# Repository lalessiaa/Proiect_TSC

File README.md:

# Open book reader
Am proiectat un E-book reader, fiind construit in jurul microcontrolerului ESP32-C6, cu un incarcator USB-C si slot microSD.

Am urmat mai multi pasi in realizarea acestui poriect:
-	Crearea schematicului 
-	Am plasat componentele pe PCB
-	Am tras circuite si rutele
-	Incarcarea elementelor 3D pe PCB
-	Crearea bateriei si a display-ului
-	Inserarea bateriei, display-ului si a PCB-ului incarcasa 3D
  
# Functionalitati hardware
## ESP32-C6 
Este microcontroller-ul , el controleaza toate componentele si gestioneaza datele.
El foloseste mai multi pini printre care :
1)	Pentru comunicarea SPI cu viteza mare si numar redus de pini avem ( card SD ):   IO6 , IO7 (MOSI) , IO10 (CS) 
2)	Pentru a intra in mod de resetare rapida si mod de programare : IO0 - Buton BOOT , IO3 - Buton Reset
3)	External NOR Flash 64MB (SPI) pentru a extinde memoria: IO2 (MISO) , IO4 (CS) , IO6 (CLK/SCK) , IO7 (MOSI) 
4)	Battery Charge Level (GPIO) : IO12 

5)	Display Type Selector (GPIO): IO14

6)	Environmental Sensor BME688 (I2C) : IO8 (SCL), IO9 (SDA) 
7)	RTC Module DS3231SN (I2C) : IO8 (SCL) - linie de ceas I2C
IO9 (SDA) - linie de date I2C
8)	EPD Power (SPI) : IO6 (CLK/SCK), IO7 (MOSI), IO2 (MISO), IO5 (CS) 

1.	Senzorul de Mediu BME688
o	Interfață: I2C
o	Măsoară temperatura, umiditatea, presiunea, și compușii volatili organici pentru monitorizarea calității aerului.
2.	Memorie Externă NOR Flash 64MB
o	Interfață: SPI
o	Descriere: Folosită pentru stocarea datelor extinse și codului care nu se încadrează în memoria internă a ESP32.
o	Are consum redus în modul standby, crescând în timpul accesărilor de date.
3.	RTC (Real Time Clock) DS3231SN
o	Interfață: I2C
o	Menține timpul real chiar și în absența alimentării principale, utilizând o baterie de backup.
4.	Modulul de Încărcare a Bateriei
o	Interfață: GPIO (pentru monitorizarea stării)
o	Gestionează încărcarea bateriei Li-Po asigurând încărcare sigură și eficientă.
o	Are un consum mic, dependent de starea bateriei și de modul de încărcare.
5.	Regulator de Tensiune LDO
o	Regulează tensiunea de intrare pentru a asigura o alimentare stabilă de 3.3V pentru toate componentele.
Comunicații și Procesare
•	SPI: Utilizat pentru comunicații rapide cu memoria flash și display-ul E-Paper. Acest protocol este ideal pentru transferul de date la viteze înalte, esențial pentru performanța display-ului și accesul rapid la date.
•	I2C: Folosit pentru comunicația cu senzori de mediu și modulul RTC, care nu necesită viteze mari de transfer dar beneficiază de simplificarea conexiunilor.

# Bill of Materials
| Componenta    | Link | Datasheet
| -------- | ------- |--------|
|ESP32_WROVER_SPARKFUN-DISCRETESEMI_MOSFET_PCH-DMG2305UX-7|https://componentsearchengine.com/part-view/DMG2305UX-7/Diodes%20Incorporated|https://www.diodes.com//assets/Datasheets/DMG2305UX.pdf|
| QWIIC_CONNECTORJS-1MM | https://www.snapeda.com/parts/PRT-14417/SparkFun/view-part/     |https://www.snapeda.com/parts/PRT-14417/SparkFun%20Electronics/datasheet/
|CPH3225A|https://www.snapeda.com/parts/CPH3225A/Seiko+Instruments/view-part/?ref=eda|https://www.snapeda.com/parts/CPH3225A/Seiko%20Instruments/datasheet/|
|BUTTON_CUSYOMV1|https://industry.panasonic.com/global/en/downloads?tab=cad&small_g_cd=203&part_no=EVQPUJ02K&q=RVZRUFVKMDJLJTdDMTMlN0MyMDMlN0MzNDU5JTdDMSU3QyU3QyU3Q2ZhbHNl|https://industry.panasonic.com/global/en/downloads?tab=catalog&small_g_cd=203&part_no=EVQPUJ02K&q=RVZRUFVKMDJLJTdDMTMlN0MyMDMlN0MzNDU5JTdDMSU3QyU3QzIlN0NmYWxzZQ%3D%3D
|ESP32_WROVER_EAGLE-LTSPICE_CC0402|https://componentsearchengine.com/part-view/CC0402MRX5R5BB106/YAGEO|https://componentsearchengine.com/Datasheets/2/CC0402MRX5R5BB106.pdf
| ESP32_WROVER_EAGLE-LTSPICE_RR0402  | https://www.snapeda.com/parts/RC0402FR-07226RL/Yageo/view-part/    |https://www.snapeda.com/parts/RC0402FR-07226RL/Yageo/datasheet/
|BD5229G-TR|https://componentsearchengine.com/part-view/BD5229G-TR/ROHM%20Semiconductor|https://datasheet.datasheetarchive.com/originals/distributors/Datasheets_SAMA/f2b9741ef86007909f138d561a359946.pdf|
|DS3231SN|https://www.snapeda.com/parts/DS3231SN%23/Analog+Devices/view-part/?ref=eda|https://www.snapeda.com/parts/DS3231SN%23/Analog%20Devices/datasheet/|
|112A-TAAR-R03_ATTEND|https://store.comet.bg/en/Catalogue/Product/43497/|https://store.comet.bg/en/Catalogue/Product/43497/|
|744043680IND_4828-WE-TPC_WRE|https://www.digikey.sg/en/models/1638515|https://www.we-online.com/components/products/datasheet/744043680.pdf
|ESP32-C6-WROOM-1-N8|https://www.snapeda.com/parts/ESP32-C6-WROOM-1-N8/Espressif+Systems/view-part/?ref=eda|https://www.snapeda.com/parts/ESP32-C6-WROOM-1-N8/Espressif%20Systems/datasheet/
|ADAFRUIT_LEDCHIP-LED0603|https://www.snapeda.com/parts/KP-1608SURCK/Kingbright/view-part/?ref=search&t=LED%200603|https://www.snapeda.com/parts/KP-1608SURCK/Kingbright/datasheet/
|MCP73831|https://www.digikey.com/en/models/1874108|https://ww1.microchip.com/downloads/aemDocuments/documents/APID/ProductDocuments/DataSheets/MCP73831-Family-Data-Sheet-DS20001984H.pdf|
|XC6220A331MR-G|https://componentsearchengine.com/part-view/XC6220A331MR-G/Torex|https://product.torexsemi.com/system/files/series/xc6220.pdf|
|ESP32_WROVER_EAGLE-LTSPICE_CC0402|https://componentsearchengine.com/Datasheets/2/CC0402MRX5R5BB106.pdf|https://componentsearchengine.com/part-view/CC0402MRX5R5BB106/YAGEO|
|ESP32C6_VARISTORCN1812|https://www.mouser.co.uk/ProductDetail/EPCOS-TDK/B72520T0350K062?qs=dEfas%2FXlABIszF52uu7vrg%3D%3D|https://www.tdk-electronics.tdk.com/inf/75/db/CTVS_14/Surge_protection_series.pdf|
|MAX17048G+T10|https://www.snapeda.com/parts/MAX17048G+T10/Analog+Devices/view-part/?ref=eda|https://www.snapeda.com/parts/MAX17048G+T10/Analog%20Devices/datasheet/|
|PGB1010603MR|https://www.snapeda.com/parts/PGB1010603MR/Littelfuse/view-part/?ref=eda|https://www.snapeda.com/parts/PGB1010603MR/Littelfuse%20Inc./datasheet/|
|RCL_CPOL-EUCT3528|https://ro.mouser.com/ProductDetail/Vishay-Sprague/TR3B106K025C1300?qs=jCGqFXxTmLdffnuDkXzk1g%3D%3D|https://www.vishay.com/docs/40080/tr3.pdf|
|FH34SRJ-24S-0.5SH_99_|https://componentsearchengine.com/part-view/XC6220A331MR-G/Torex|https://product.torexsemi.com/system/files/series/xc6220.pdf|
|SAMACSYS_PARTS_USB4110-GF-A|https://componentsearchengine.com/part-view/USB4110-GF-A/GCT%20(GLOBAL%20CONNECTOR%20TECHNOLOGY)|https://gct.co/files/drawings/usb4110.pdf|
|SI1308EDL-T1-GE3|https://componentsearchengine.com/part-view/SI1308EDL-T1-GE3/Vishay|https://componentsearchengine.com/Datasheets/1/SI1308EDL-T1-GE3.pdf|
|MBR0530|https://ro.mouser.com/ProductDetail/KYOCERA-AVX/SD0805S020S1R0?qs=jCA%252BPfw4LHbpkAoSnwrdjw%3D%3D|https://ro.mouser.com/datasheet/2/40/schottky-3165252.pdf|
|SJ|https://grabcad.com/library/solder-jumpers-1||
|W25Q512JVEIQ|https://www.snapeda.com/parts/W25Q512JVEIQ/Winbond+Electronics/view-part/?ref=eda|https://www.snapeda.com/parts/W25Q512JVEIQ/Winbond%20Electronics/datasheet/|
|ESP32_WROVER_BME680_BME680|https://www.snapeda.com/parts/BME680/Bosch/view-part/?welcome=home|https://www.snapeda.com/parts/BME680/Bosch%20Sensortec/datasheet/|
|CPH3225A|https://www.snapeda.com/parts/CPH3225A/Seiko+Instruments/view-part/?ref=eda|https://www.snapeda.com/parts/CPH3225A/Seiko%20Instruments/datasheet/|
|USBLC6-2SC6Y|https://www.snapeda.com/parts/USBLC6-2SC6Y/STMicroelectronics/view-part/?ref=eda|https://www.snapeda.com/parts/USBLC6-2SC6Y/STMicroelectronics/datasheet/|

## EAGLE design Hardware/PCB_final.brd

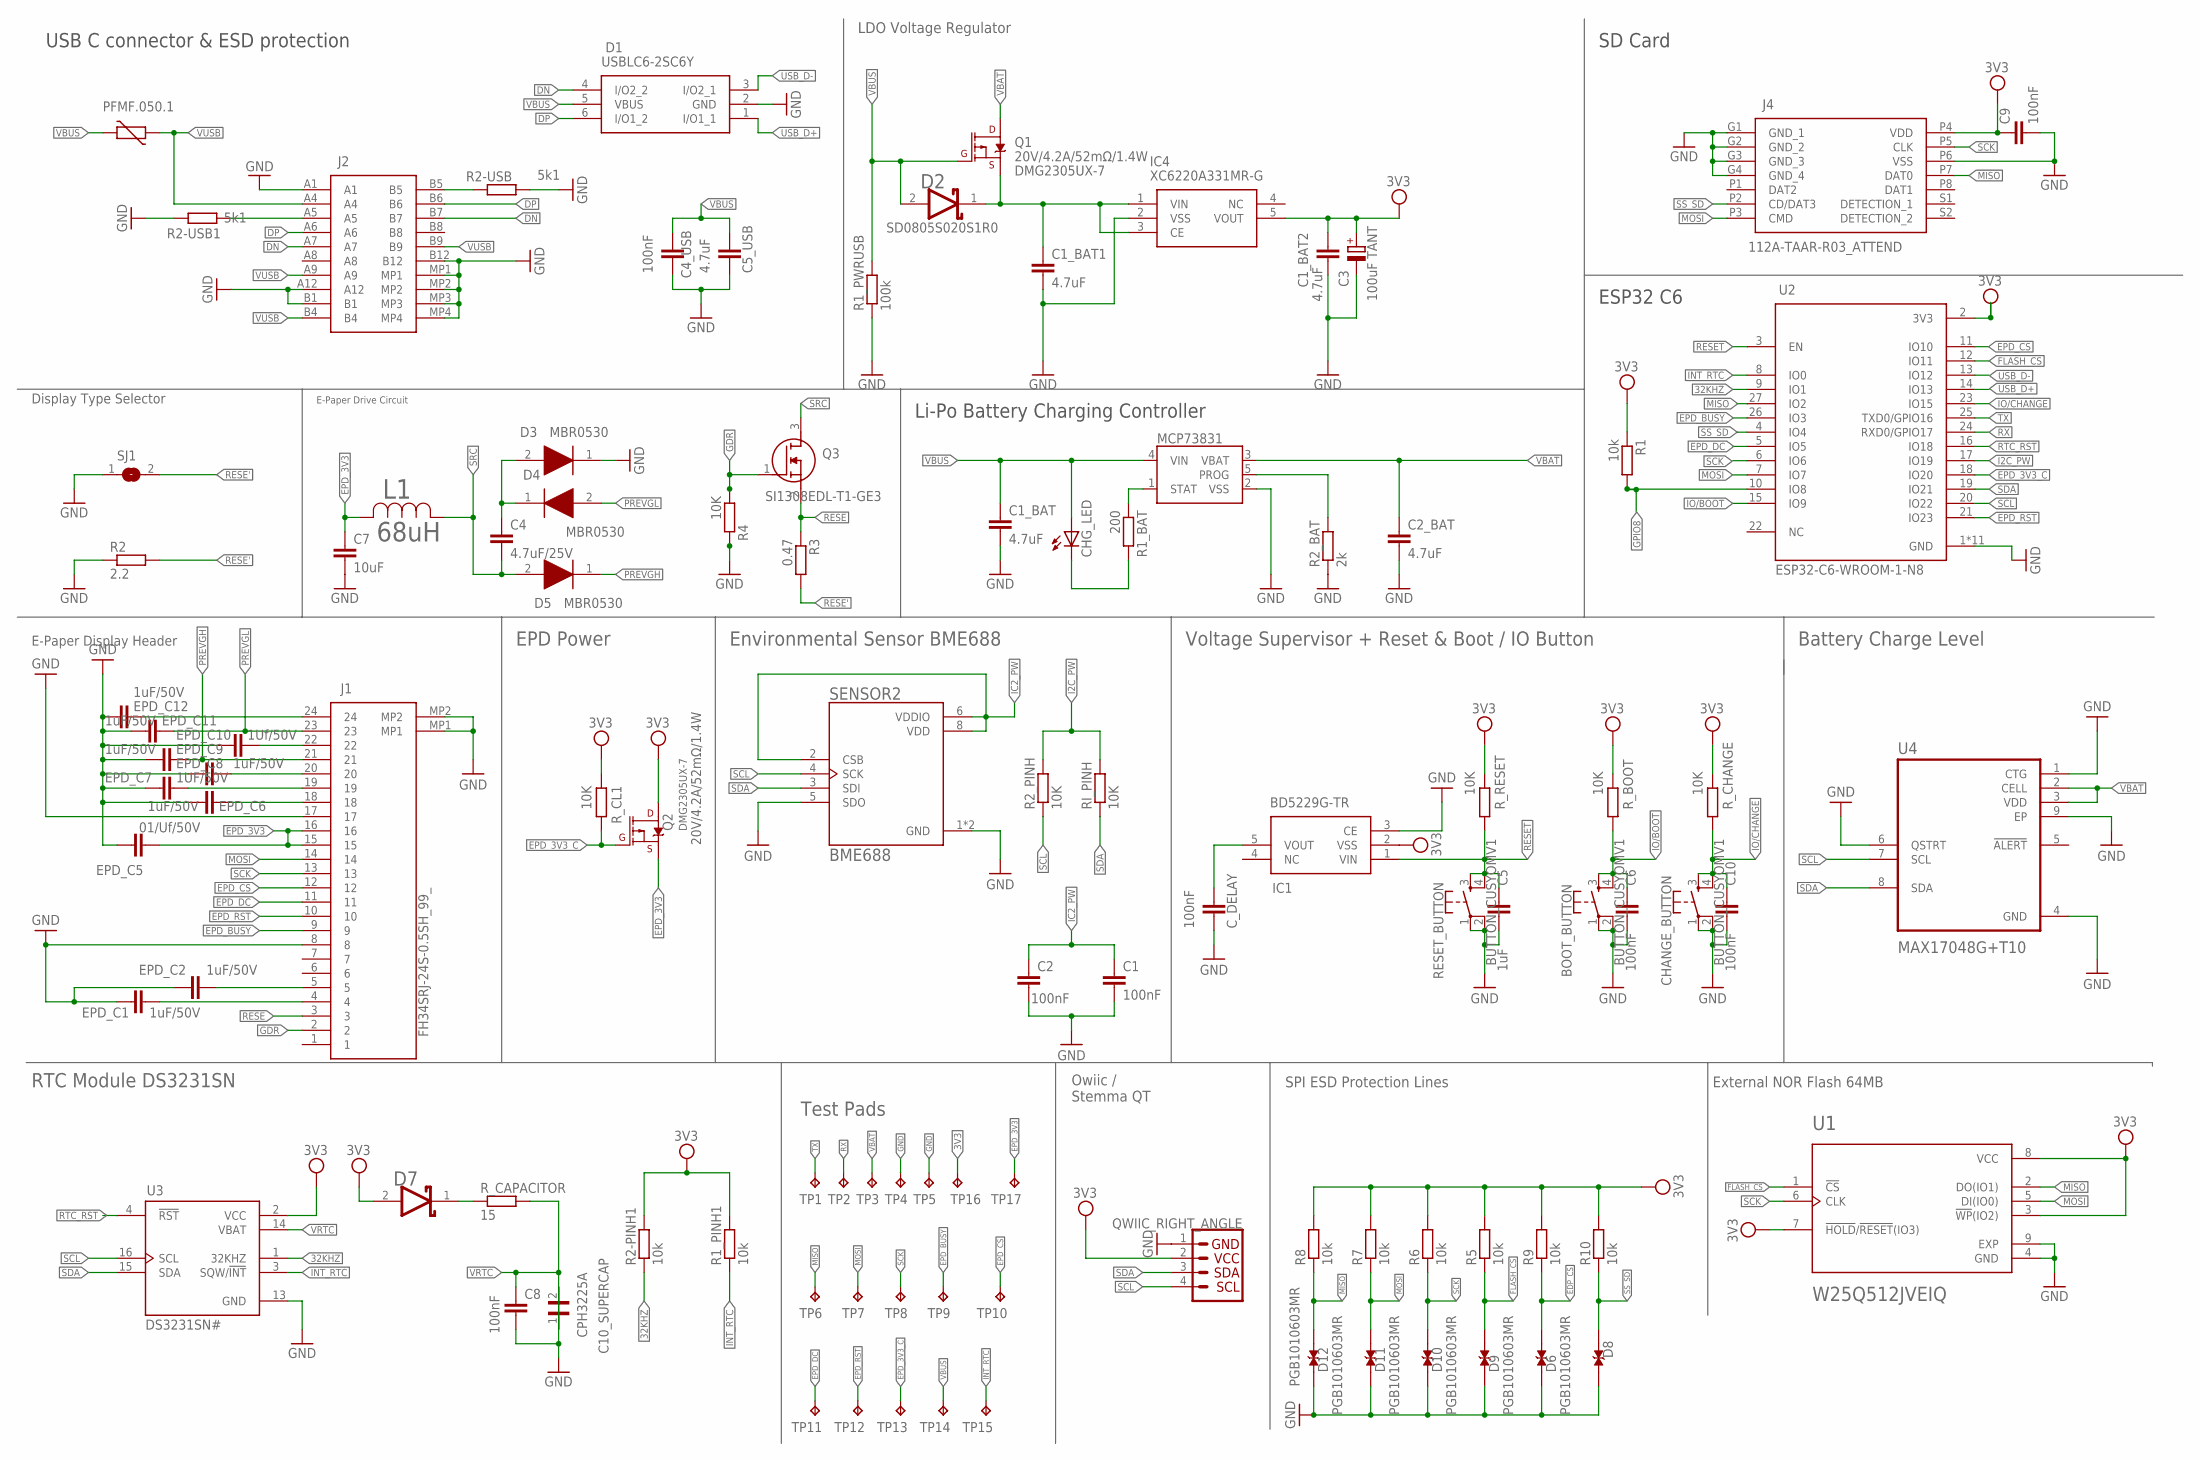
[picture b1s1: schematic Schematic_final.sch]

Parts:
BOOT_BUTTON: BUTTON_CUSYOMV1; MYBUTTON
C1, C2, C6, C8, C10: 100nF; ESP32_WROVER_EAGLE-LTSPICE_C0402
C1_BAT, C1_BAT2, C2_BAT: 4.7uF; ESP32_WROVER_EAGLE-LTSPICE_C0402
C1_BAT1, C5_USB: 4.7uF; EAGLE-LTSPICE_C0402
C3: 100uF TANT; RCL_CT3528
C4: 4.7uF/25V; ESP32_WROVER_EAGLE-LTSPICE_C0402
C4_USB, C9: 100nF; EAGLE-LTSPICE_C0402
C5: 1uF; ESP32_WROVER_EAGLE-LTSPICE_C0402
C7: 10uF; ESP32_WROVER_EAGLE-LTSPICE_C0402
C10_SUPERCAP: CPH3225A; CAPCP3225X100N
CHANGE_BUTTON: BUTTON_CUSYOMV1; MYBUTTON
CHG_LED: ADAFRUIT_LEDCHIP-LED0603; ADAFRUIT_CHIP-LED0603
C_DELAY: 100nF; ESP32_WROVER_EAGLE-LTSPICE_C0402
D1: USBLC6-2SC6Y; SOT95P280X145-6N
D2, D7: ESP32_WROVER_AVX---SD0805S020S1R0_AVX_SD0805S020S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; ESP32_WROVER_AVX---SD0805S020S1R0_AVX_SD0805S020S1R0_0
D3, D4, D5: MBR0530; SOD3716X135N
D6, D8, D9, D10, D11, D12: PGB1010603MR; DIOC1608X36N
EPD_C1, EPD_C2, EPD_C6, EPD_C8, EPD_C9, EPD_C11, EPD_C12: 1uF/50V; ESP32_WROVER_EAGLE-LTSPICE_C0402
EPD_C5: 01/Uf/50V; ESP32_WROVER_EAGLE-LTSPICE_C0402
EPD_C7: 1UF/50V; ESP32_WROVER_EAGLE-LTSPICE_C0402
EPD_C10: 1Uf/50V; ESP32_WROVER_EAGLE-LTSPICE_C0402
IC1: BD5229G-TR; SOT95P280X120-5N
IC4: XC6220A331MR-G; SOT95P280X120-5N
J1: FH34SRJ-24S-0.5SH_99_; FH34SRJ24S05SH99
J2: SAMACSYS_PARTS_USB4110-GF-A; SAMACSYS_PARTS_USB4110GFA
J3: QWIIC_RIGHT_ANGLE; JST04_1MM_RA
J4: 112A-TAAR-R03_ATTEND; 112ATAARR03ATTEND
L1: 68uH; IND_4828-WE-TPC_WRE
MCP73831: ESP32_WROVER_SPARKFUN-IC-POWER_MCP73831; ESP32_WROVER_SPARKFUN-IC-POWER_SOT23-5
PFMF.050.1: ESP32C6_VARISTORCN1812; ESP32C6_VARISTOR_CT/CN1812
Q1, Q2: 20V/4.2A/52mΩ/1.4W; ESP32_WROVER_SPARKFUN-DISCRETESEMI_SOT23-3
Q3: SI1308EDL-T1-GE3; SOT65P210X110-3N
R1, R1_PINH1, R2-PINH1, R5, R6, R7, R8, R9, R10: 10k; ESP32_WROVER_EAGLE-LTSPICE_R0402
R1_BAT: 200; ESP32_WROVER_EAGLE-LTSPICE_R0402
R1_PWRUSB: 100k; ESP32_WROVER_EAGLE-LTSPICE_R0402
R2: 2.2; ESP32_WROVER_EAGLE-LTSPICE_R0402
R2-USB, R2-USB1: 5k1; ESP32_WROVER_EAGLE-LTSPICE_R0402
R2_BAT: 2k; ESP32_WROVER_EAGLE-LTSPICE_R0402
R2_PINH, R4: 10K; ESP32_WROVER_EAGLE-LTSPICE_R0402
R3: 0.47; ESP32_WROVER_EAGLE-LTSPICE_R0402
RESET_BUTTON: BUTTON_CUSYOMV1; MYBUTTON
RI_PINH: 10K; ESP32_WROVER_EAGLE-LTSPICE_R0402
R_BOOT: 10K; ESP32_WROVER_EAGLE-LTSPICE_R0402
R_CAPACITOR: 15; ESP32_WROVER_EAGLE-LTSPICE_R0402
R_CHANGE: 10K; ESP32_WROVER_EAGLE-LTSPICE_R0402
R_CL1: 10K; ESP32_WROVER_EAGLE-LTSPICE_R0402
R_RESET: 10K; ESP32_WROVER_EAGLE-LTSPICE_R0402
SENSOR2: BME688; ESP32_WROVER_BME680_PSON80P300X300X100-8N
SJ1: SJ
TP1, TP2, TP3, TP4, TP5, TP6, TP7, TP8, TP9, TP10, TP11, TP12, TP13, TP14, TP15, TP16, TP17: TPTP20R; TP20R
U1: W25Q512JVEIQ; SON127P600X800X80-9N
U2: ESP32-C6-WROOM-1-N8; XCVR_ESP32-C6-WROOM-1-N8
U3: DS3231SN#; SOIC127P1032X265-16N
U4: MAX17048G+T10; SON50P200X200X80-9N

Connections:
3V3: C1_BAT2.1, C3.+, C9.1, D7.2 (ANODE), IC1.2 (VSS), IC4.5 (VOUT), J3.2, J4.P4 (VDD), Q2.3 (D), R1.1, R1_PINH1.2, R2-PINH1.2, R5.2, R6.2, R7.2, R8.2, R9.2, R10.2, R_BOOT.2, R_CHANGE.2, R_CL1.2, R_RESET.2, TP16.TP, U1.3 (!WP!(IO2)), U1.7 (!HOLD!/!RESET!(IO3)), U1.8 (VCC), U2.2 (3V3), U3.2 (VCC)
32KHZ: R2-PINH1.1, U2.9 (IO1), U3.1 (32KHZ)
DN: J2.A7
DP: J2.A6
EDP_CS: D9.2, R9.1
EPD_3V3: C7.1, EPD_C5.2, J1.15, J1.16, L1.2, Q2.2 (S), TP17.TP
EPD_3V3_C: Q2.1 (G), R_CL1.1, TP13.TP, U2.18 (IO20)
EPD_BUSY: J1.9, TP9.TP, U2.26 (IO3)
EPD_CS: J1.12, TP10.TP, U2.11 (IO10)
EPD_DC: J1.11, TP11.TP, U2.5 (IO5)
EPD_RST: J1.10, TP12.TP, U2.21 (IO23)
FLASH_CS: D10.2, R5.1, U1.1 (!CS), U2.12 (IO11)
GDR: J1.2, Q3.1 (G), R4.2
GND: BOOT_BUTTON.1, BOOT_BUTTON.2, C1.2, C1_BAT.2, C1_BAT1.2, C1_BAT2.2, C2.2, C2_BAT.2, C3.-, C4_USB.2, C5.2, C5_USB.2, C6.2, C7.2, C8.2, C9.2, C10.2, C10_SUPERCAP.2, CHANGE_BUTTON.1, CHANGE_BUTTON.2, C_DELAY.2, D1.2 (GND), D3.1 (K), D6.1, D8.1, D9.1, D10.1, D11.1, D12.1, EPD_C1.1, EPD_C2.1, EPD_C5.1, EPD_C6.2, EPD_C7.2, EPD_C8.2, EPD_C9.2, EPD_C10.2, EPD_C11.2, EPD_C12.2, IC1.3 (CE), IC4.2 (VSS), J1.8, J1.17, J1.MP1, J1.MP2, J2.A1, J2.A12, J2.B1, J2.B12, J2.MP1, J2.MP2, J2.MP3, J2.MP4, J3.1, J4.G1 (GND_1), J4.G2 (GND_2), J4.G3 (GND_3), J4.G4 (GND_4), J4.P6 (VSS), MCP73831.2 (VSS), R1_PWRUSB.1, R2.1, R2-USB.2, R2-USB1.1, R2_BAT.1, R4.1, RESET_BUTTON.1, RESET_BUTTON.2, SENSOR2.1 (GND), SENSOR2.5 (SDO), SENSOR2.7 (GND), SJ1.1, TP4.TP, TP5.TP, U1.4 (GND), U1.9 (EXP), U2.1 (GND), U2.28 (GND), U2.29_1 (GND), U2.29_2 (GND), U2.29_3 (GND), U2.29_4 (GND), U2.29_5 (GND), U2.29_6 (GND), U2.29_7 (GND), U2.29_8 (GND), U2.29_9 (GND), U3.13 (GND), U4.1 (CTG), U4.4 (GND), U4.6 (QSTRT), U4.9 (EP)
GPIO8: R1.2, U2.10 (IO8)
I2C_PW: R2_PINH.2, RI_PINH.2, U2.17 (IO19)
IC2_PW: C1.1, C2.1, SENSOR2.2 (CSB), SENSOR2.6 (VDDIO), SENSOR2.8 (VDD)
INT_RTC: R1_PINH1.1, TP15.TP, U2.8 (IO0), U3.3 (SQW/!INT)
IO/BOOT: BOOT_BUTTON.3, BOOT_BUTTON.4, C6.1, R_BOOT.1, U2.15 (IO9)
IO/CHANGE: C10.1, CHANGE_BUTTON.3, CHANGE_BUTTON.4, R_CHANGE.1, U2.23 (IO15)
MISO: D8.2, J4.P7 (DAT0), R8.1, TP6.TP, U1.2 (DO(IO1))
MOSI: D12.2, J1.14, J4.P3 (CMD), R7.1, TP7.TP, U1.5 (DI(IO0))
unnamed: J2.B5, R2-USB.1
unnamed: J2.A5, R2-USB1.2
unnamed: C_DELAY.1, IC1.5 (VOUT)
unnamed: EPD_C1.2, J1.4
unnamed: EPD_C2.2, J1.5
unnamed: EPD_C6.1, J1.18
unnamed: EPD_C7.1, J1.19
unnamed: EPD_C8.1, J1.20
unnamed: C4_USB.1, C5_USB.1
unnamed: EPD_C10.1, J1.22
unnamed: C1_BAT1.1, D2.1 (CATHODE), IC4.1 (VIN), IC4.3 (CE), Q1.2 (S)
unnamed: EPD_C12.1, J1.24
unnamed: D2.2 (ANODE), Q1.1 (G), R1_PWRUSB.2
unnamed: C4.2, D5.2 (A), L1.1
unnamed: C4.1, D3.2 (A), D4.1 (K)
unnamed: MCP73831.1 (STAT), R1_BAT.1
unnamed: CHG_LED.C, R1_BAT.2
unnamed: C1_BAT.1, CHG_LED.A, MCP73831.4 (VIN)
unnamed: MCP73831.5 (PROG), R2_BAT.2
unnamed: D7.1 (CATHODE), R_CAPACITOR.1
PREVGH: D5.1 (K), EPD_C9.1, J1.21
PREVGL: D4.2 (A), EPD_C11.1, J1.23
RESE: J1.3, Q3.2 (S), R3.1
RESE': SJ1.2
RESET: C5.1, IC1.1 (VIN), RESET_BUTTON.3, RESET_BUTTON.4, R_RESET.1, U2.3 (EN)
RTC_RST: U2.16 (IO18), U3.4 (!RST)
RX: TP2.TP, U2.24 (RXD0/GPIO17)
SCK: D11.2, J1.13, J4.P5 (CLK), R6.1, TP8.TP, U1.6 (CLK)
SCL: J3.4, R2_PINH.1, SENSOR2.4 (SCK), U2.20 (IO22), U3.16 (SCL), U4.7 (SCL)
SDA: J3.3, RI_PINH.1, SENSOR2.3 (SDI), U2.19 (IO21), U3.15 (SDA), U4.8 (SDA)
SRC: Q3.3 (D)
SS_SD: D6.2, J4.P2 (CD/DAT3), R10.1
TX: TP1.TP, U2.25 (TXD0/GPIO16)
USB_D+: D1.1 (I/O1_1), U2.14 (IO13)
USB_D-: D1.3 (I/O2_1), U2.13 (IO12)
VBAT: Q1.3 (D), TP3.TP, U4.2 (CELL), U4.3 (VDD)
VBBAT: C2_BAT.1, MCP73831.3 (VBAT)
VBUS: PFMF.050.1.2, TP14.TP
VRTC: C8.1, C10_SUPERCAP.1, R_CAPACITOR.2, U3.14 (VBAT)
VUSB: J2.A4, PFMF.050.1.1

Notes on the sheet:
DMG2305UX-7
USB C connector & ESD protection
SD Card
Li-Po Battery Charging Controller
ESP32 C6
Test Pads
EPD Power
Environmental Sensor BME688
Voltage Supervisor + Reset & Boot / IO Button
Battery Charge Level
SD0805S020S1R0
RTC Module DS3231SN
E-Paper Display Header
Display Type Selector
E-Paper Drive Circuit
SPI ESD Protection Lines
Owiic / Stemma QT
External NOR Flash 64MB
LDO Voltage Regulator

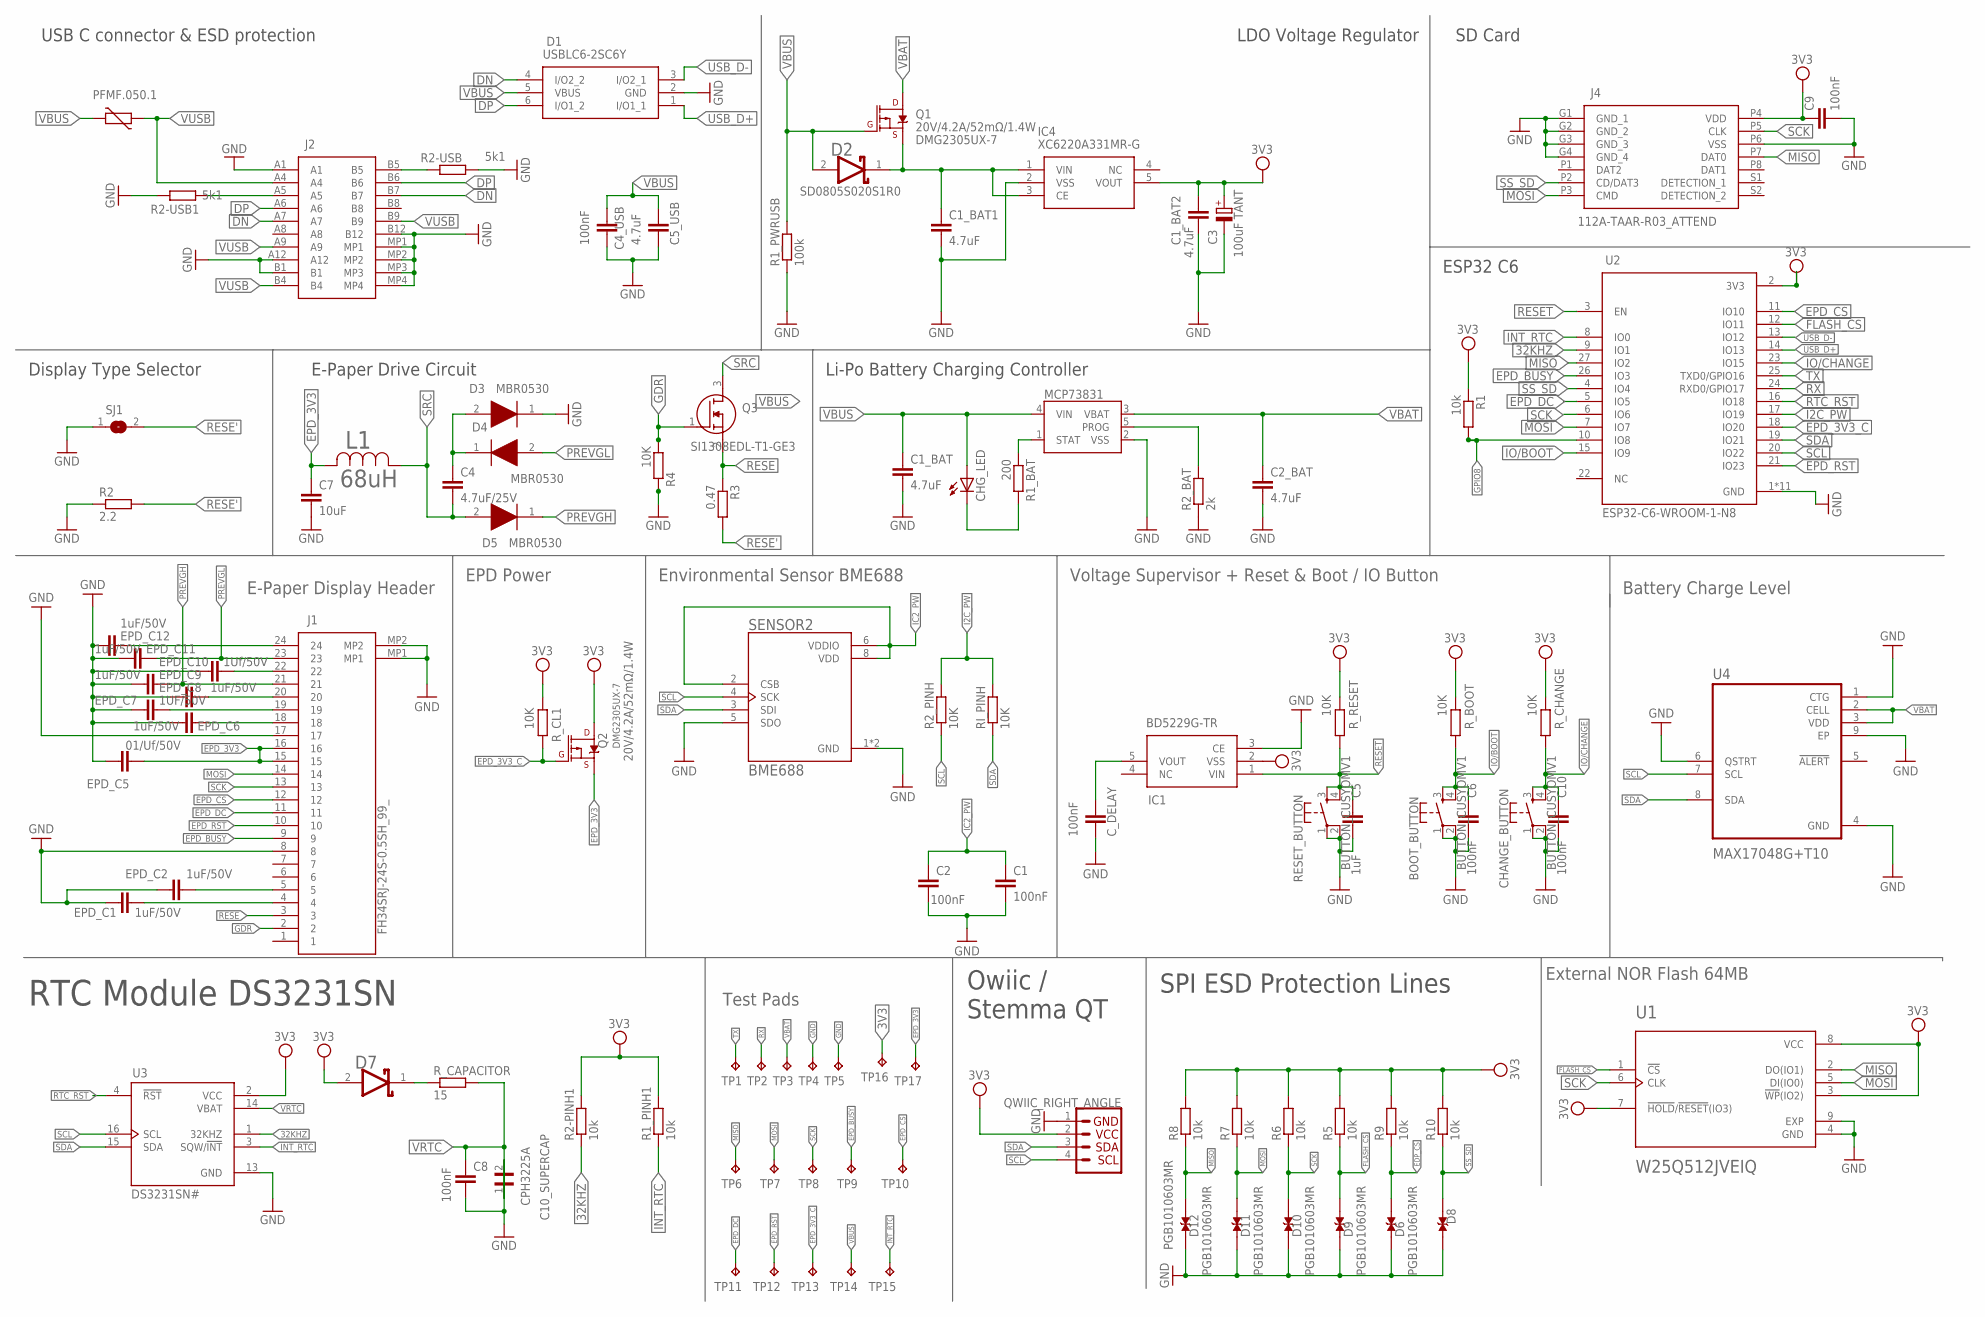
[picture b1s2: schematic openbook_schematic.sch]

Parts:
BOOT_BUTTON: BUTTON_CUSYOMV1; MYBUTTON
C1, C2, C6, C8, C10: 100nF; ESP32_WROVER_EAGLE-LTSPICE_C0402
C1_BAT, C1_BAT2, C2_BAT: 4.7uF; ESP32_WROVER_EAGLE-LTSPICE_C0402
C1_BAT1, C5_USB: 4.7uF; EAGLE-LTSPICE_C0402
C3: 100uF TANT; RCL_CT3528
C4: 4.7uF/25V; ESP32_WROVER_EAGLE-LTSPICE_C0402
C4_USB, C9: 100nF; EAGLE-LTSPICE_C0402
C5: 1uF; ESP32_WROVER_EAGLE-LTSPICE_C0402
C7: 10uF; ESP32_WROVER_EAGLE-LTSPICE_C0402
C10_SUPERCAP: CPH3225A; CAPCP3225X100N
CHANGE_BUTTON: BUTTON_CUSYOMV1; MYBUTTON
CHG_LED: ADAFRUIT_LEDCHIP-LED0603; ADAFRUIT_CHIP-LED0603
C_DELAY: 100nF; ESP32_WROVER_EAGLE-LTSPICE_C0402
D1: USBLC6-2SC6Y; SOT95P280X145-6N
D2, D7: ESP32_WROVER_AVX---SD0805S020S1R0_AVX_SD0805S020S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; ESP32_WROVER_AVX---SD0805S020S1R0_AVX_SD0805S020S1R0_0
D3, D4, D5: MBR0530; SOD3716X135N
D6, D8, D9, D10, D11, D12: PGB1010603MR; DIOC1608X36N
EPD_C1, EPD_C2, EPD_C6, EPD_C8, EPD_C9, EPD_C11, EPD_C12: 1uF/50V; ESP32_WROVER_EAGLE-LTSPICE_C0402
EPD_C5: 01/Uf/50V; ESP32_WROVER_EAGLE-LTSPICE_C0402
EPD_C7: 1UF/50V; ESP32_WROVER_EAGLE-LTSPICE_C0402
EPD_C10: 1Uf/50V; ESP32_WROVER_EAGLE-LTSPICE_C0402
IC1: BD5229G-TR; SOT95P280X120-5N
IC4: XC6220A331MR-G; SOT95P280X120-5N
J1: FH34SRJ-24S-0.5SH_99_; FH34SRJ24S05SH99
J2: SAMACSYS_PARTS_USB4110-GF-A; SAMACSYS_PARTS_USB4110GFA
J3: QWIIC_RIGHT_ANGLE; JST04_1MM_RA
J4: 112A-TAAR-R03_ATTEND; 112ATAARR03ATTEND
L1: 68uH; IND_4828-WE-TPC_WRE
MCP73831: ESP32_WROVER_SPARKFUN-IC-POWER_MCP73831; ESP32_WROVER_SPARKFUN-IC-POWER_SOT23-5
PFMF.050.1: ESP32C6_VARISTORCN1812; ESP32C6_VARISTOR_CT/CN1812
Q1, Q2: 20V/4.2A/52mΩ/1.4W; ESP32_WROVER_SPARKFUN-DISCRETESEMI_SOT23-3
Q3: SI1308EDL-T1-GE3; SOT65P210X110-3N
R1, R1_PINH1, R2-PINH1, R5, R6, R7, R8, R9, R10: 10k; ESP32_WROVER_EAGLE-LTSPICE_R0402
R1_BAT: 200; ESP32_WROVER_EAGLE-LTSPICE_R0402
R1_PWRUSB: 100k; ESP32_WROVER_EAGLE-LTSPICE_R0402
R2: 2.2; ESP32_WROVER_EAGLE-LTSPICE_R0402
R2-USB, R2-USB1: 5k1; ESP32_WROVER_EAGLE-LTSPICE_R0402
R2_BAT: 2k; ESP32_WROVER_EAGLE-LTSPICE_R0402
R2_PINH, R4: 10K; ESP32_WROVER_EAGLE-LTSPICE_R0402
R3: 0.47; ESP32_WROVER_EAGLE-LTSPICE_R0402
RESET_BUTTON: BUTTON_CUSYOMV1; MYBUTTON
RI_PINH: 10K; ESP32_WROVER_EAGLE-LTSPICE_R0402
R_BOOT: 10K; ESP32_WROVER_EAGLE-LTSPICE_R0402
R_CAPACITOR: 15; ESP32_WROVER_EAGLE-LTSPICE_R0402
R_CHANGE: 10K; ESP32_WROVER_EAGLE-LTSPICE_R0402
R_CL1: 10K; ESP32_WROVER_EAGLE-LTSPICE_R0402
R_RESET: 10K; ESP32_WROVER_EAGLE-LTSPICE_R0402
SENSOR2: BME688; ESP32_WROVER_BME680_PSON80P300X300X100-8N
SJ1: SJ
TP1, TP2, TP3, TP4, TP5, TP6, TP7, TP8, TP9, TP10, TP11, TP12, TP13, TP14, TP15, TP16, TP17: TPTP20R; TP20R
U1: W25Q512JVEIQ; SON127P600X800X80-9N
U2: ESP32-C6-WROOM-1-N8; XCVR_ESP32-C6-WROOM-1-N8
U3: DS3231SN#; SOIC127P1032X265-16N
U4: MAX17048G+T10; SON50P200X200X80-9N

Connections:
3V3: C1_BAT2.1, C3.+, C9.1, D7.2 (ANODE), IC1.2 (VSS), IC4.5 (VOUT), J3.2, J4.P4 (VDD), Q2.3 (D), R1.1, R1_PINH1.2, R2-PINH1.2, R5.2, R6.2, R7.2, R8.2, R9.2, R10.2, R_BOOT.2, R_CHANGE.2, R_CL1.2, R_RESET.2, TP16.TP, U1.3 (!WP!(IO2)), U1.7 (!HOLD!/!RESET!(IO3)), U1.8 (VCC), U2.2 (3V3), U3.2 (VCC)
32KHZ: R2-PINH1.1, U2.9 (IO1), U3.1 (32KHZ)
DN: J2.A7
DP: J2.A6
EDP_CS: D9.2, R9.1
EPD_3V3: C7.1, EPD_C5.2, J1.15, J1.16, L1.2, Q2.2 (S), TP17.TP
EPD_3V3_C: Q2.1 (G), R_CL1.1, TP13.TP, U2.18 (IO20)
EPD_BUSY: J1.9, TP9.TP, U2.26 (IO3)
EPD_CS: J1.12, TP10.TP, U2.11 (IO10)
EPD_DC: J1.11, TP11.TP, U2.5 (IO5)
EPD_RST: J1.10, TP12.TP, U2.21 (IO23)
FLASH_CS: D10.2, R5.1, U1.1 (!CS), U2.12 (IO11)
GDR: J1.2, Q3.1 (G), R4.2
GND: BOOT_BUTTON.1, BOOT_BUTTON.2, C1.2, C1_BAT.2, C1_BAT1.2, C1_BAT2.2, C2.2, C2_BAT.2, C3.-, C4_USB.2, C5.2, C5_USB.2, C6.2, C7.2, C8.2, C9.2, C10.2, C10_SUPERCAP.2, CHANGE_BUTTON.1, CHANGE_BUTTON.2, C_DELAY.2, D1.2 (GND), D3.1 (K), D6.1, D8.1, D9.1, D10.1, D11.1, D12.1, EPD_C1.1, EPD_C2.1, EPD_C5.1, EPD_C6.2, EPD_C7.2, EPD_C8.2, EPD_C9.2, EPD_C10.2, EPD_C11.2, EPD_C12.2, IC1.3 (CE), IC4.2 (VSS), J1.8, J1.17, J1.MP1, J1.MP2, J2.A1, J2.A12, J2.B1, J2.B12, J2.MP1, J2.MP2, J2.MP3, J2.MP4, J3.1, J4.G1 (GND_1), J4.G2 (GND_2), J4.G3 (GND_3), J4.G4 (GND_4), J4.P6 (VSS), MCP73831.2 (VSS), R1_PWRUSB.1, R2.1, R2-USB.2, R2-USB1.1, R2_BAT.1, R4.1, RESET_BUTTON.1, RESET_BUTTON.2, SENSOR2.1 (GND), SENSOR2.5 (SDO), SENSOR2.7 (GND), SJ1.1, TP4.TP, TP5.TP, U1.4 (GND), U1.9 (EXP), U2.1 (GND), U2.28 (GND), U2.29_1 (GND), U2.29_2 (GND), U2.29_3 (GND), U2.29_4 (GND), U2.29_5 (GND), U2.29_6 (GND), U2.29_7 (GND), U2.29_8 (GND), U2.29_9 (GND), U3.13 (GND), U4.1 (CTG), U4.4 (GND), U4.6 (QSTRT), U4.9 (EP)
GPIO8: R1.2, U2.10 (IO8)
I2C_PW: R2_PINH.2, RI_PINH.2, U2.17 (IO19)
IC2_PW: C1.1, C2.1, SENSOR2.2 (CSB), SENSOR2.6 (VDDIO), SENSOR2.8 (VDD)
INT_RTC: R1_PINH1.1, TP15.TP, U2.8 (IO0), U3.3 (SQW/!INT)
IO/BOOT: BOOT_BUTTON.3, BOOT_BUTTON.4, C6.1, R_BOOT.1, U2.15 (IO9)
IO/CHANGE: C10.1, CHANGE_BUTTON.3, CHANGE_BUTTON.4, R_CHANGE.1, U2.23 (IO15)
MISO: D8.2, J4.P7 (DAT0), R8.1, TP6.TP, U1.2 (DO(IO1))
MOSI: D12.2, J1.14, J4.P3 (CMD), R7.1, TP7.TP, U1.5 (DI(IO0))
unnamed: J2.B5, R2-USB.1
unnamed: J2.A5, R2-USB1.2
unnamed: C_DELAY.1, IC1.5 (VOUT)
unnamed: EPD_C1.2, J1.4
unnamed: EPD_C2.2, J1.5
unnamed: EPD_C6.1, J1.18
unnamed: EPD_C7.1, J1.19
unnamed: EPD_C8.1, J1.20
unnamed: C4_USB.1, C5_USB.1
unnamed: EPD_C10.1, J1.22
unnamed: C1_BAT1.1, D2.1 (CATHODE), IC4.1 (VIN), IC4.3 (CE), Q1.2 (S)
unnamed: EPD_C12.1, J1.24
unnamed: D2.2 (ANODE), Q1.1 (G), R1_PWRUSB.2
unnamed: C4.2, D5.2 (A), L1.1
unnamed: C4.1, D3.2 (A), D4.1 (K)
unnamed: MCP73831.1 (STAT), R1_BAT.1
unnamed: CHG_LED.C, R1_BAT.2
unnamed: C1_BAT.1, CHG_LED.A, MCP73831.4 (VIN)
unnamed: MCP73831.5 (PROG), R2_BAT.2
unnamed: D7.1 (CATHODE), R_CAPACITOR.1
PREVGH: D5.1 (K), EPD_C9.1, J1.21
PREVGL: D4.2 (A), EPD_C11.1, J1.23
RESE: J1.3, Q3.2 (S), R3.1
RESE': SJ1.2
RESET: C5.1, IC1.1 (VIN), RESET_BUTTON.3, RESET_BUTTON.4, R_RESET.1, U2.3 (EN)
RTC_RST: U2.16 (IO18), U3.4 (!RST)
RX: TP2.TP, U2.24 (RXD0/GPIO17)
SCK: D11.2, J1.13, J4.P5 (CLK), R6.1, TP8.TP, U1.6 (CLK)
SCL: J3.4, R2_PINH.1, SENSOR2.4 (SCK), U2.20 (IO22), U3.16 (SCL), U4.7 (SCL)
SDA: J3.3, RI_PINH.1, SENSOR2.3 (SDI), U2.19 (IO21), U3.15 (SDA), U4.8 (SDA)
SRC: Q3.3 (D)
SS_SD: D6.2, J4.P2 (CD/DAT3), R10.1
TX: TP1.TP, U2.25 (TXD0/GPIO16)
USB_D+: D1.1 (I/O1_1), U2.14 (IO13)
USB_D-: D1.3 (I/O2_1), U2.13 (IO12)
VBAT: Q1.3 (D), TP3.TP, U4.2 (CELL), U4.3 (VDD)
VBBAT: C2_BAT.1, MCP73831.3 (VBAT)
VBUS: PFMF.050.1.2, TP14.TP
VRTC: C8.1, C10_SUPERCAP.1, R_CAPACITOR.2, U3.14 (VBAT)
VUSB: J2.A4, PFMF.050.1.1

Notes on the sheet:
DMG2305UX-7
USB C connector & ESD protection
LDO Voltage Regulator
SD Card
Display Type Selector
E-Paper Drive Circuit
Li-Po Battery Charging Controller
ESP32 C6
Owiic / Stemma QT
RTC Module DS3231SN
SPI ESD Protection Lines
External NOR Flash 64MB
Test Pads
EPD Power
Environmental Sensor BME688
Voltage Supervisor + Reset & Boot / IO Button
Battery Charge Level
E-Paper Display Header
SD0805S020S1R0

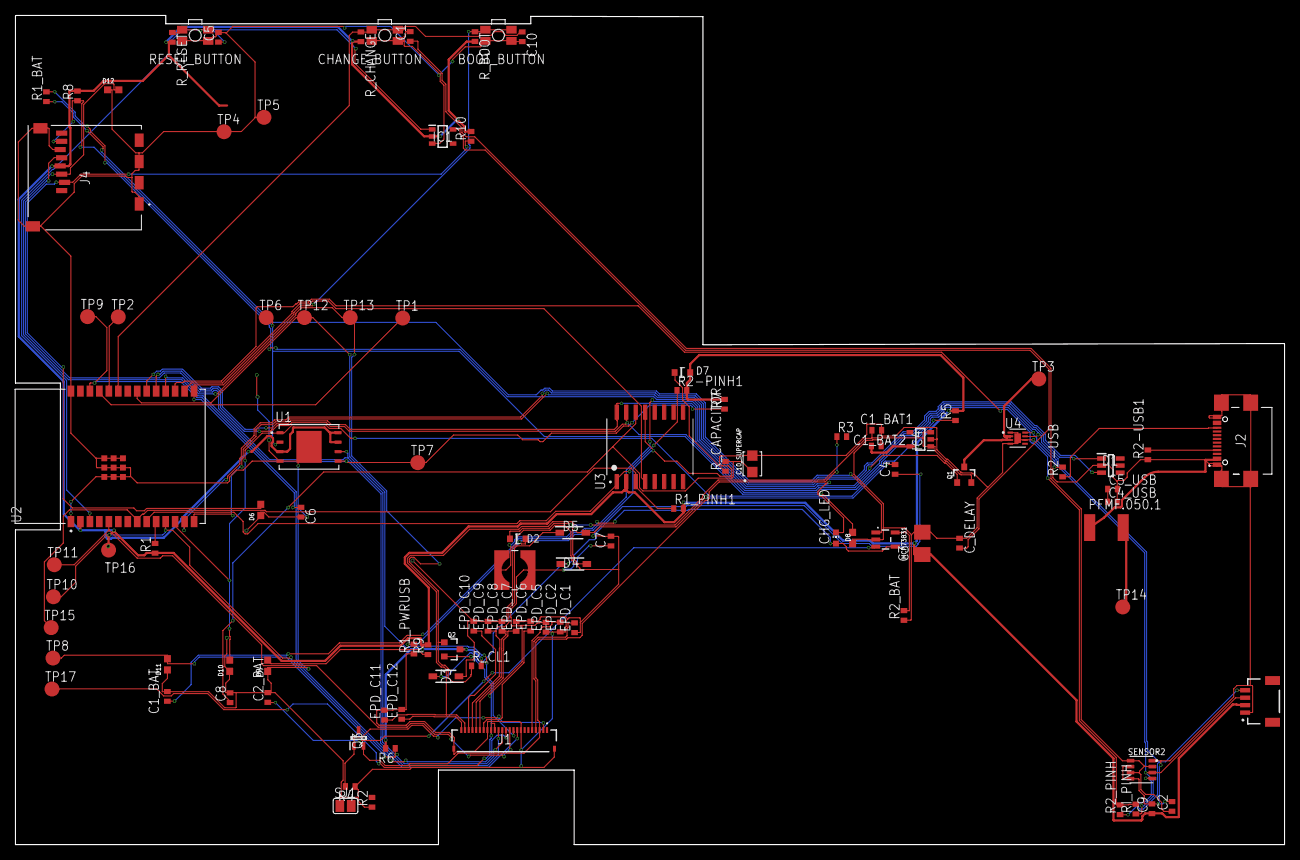
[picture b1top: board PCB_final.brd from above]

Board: 2 copper layers, 170.2 x 111.2 mm, 103 parts (0 on the bottom side), 58 nets.

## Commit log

2025-04-06 Create LICENSE
2025-04-06 Create empty
2025-04-06 README.md

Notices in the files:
parts and their libraries:
COPYRIGHT: Copyright (C) 2024 Ultra Librarian. All rights reserved.
